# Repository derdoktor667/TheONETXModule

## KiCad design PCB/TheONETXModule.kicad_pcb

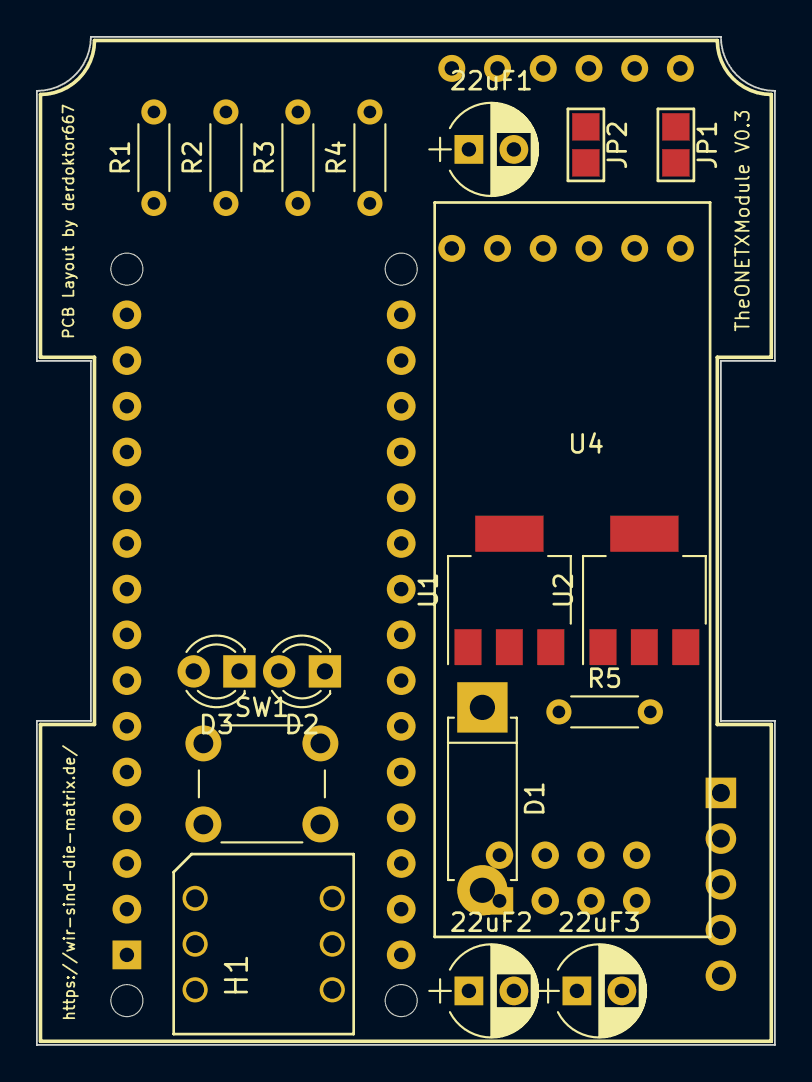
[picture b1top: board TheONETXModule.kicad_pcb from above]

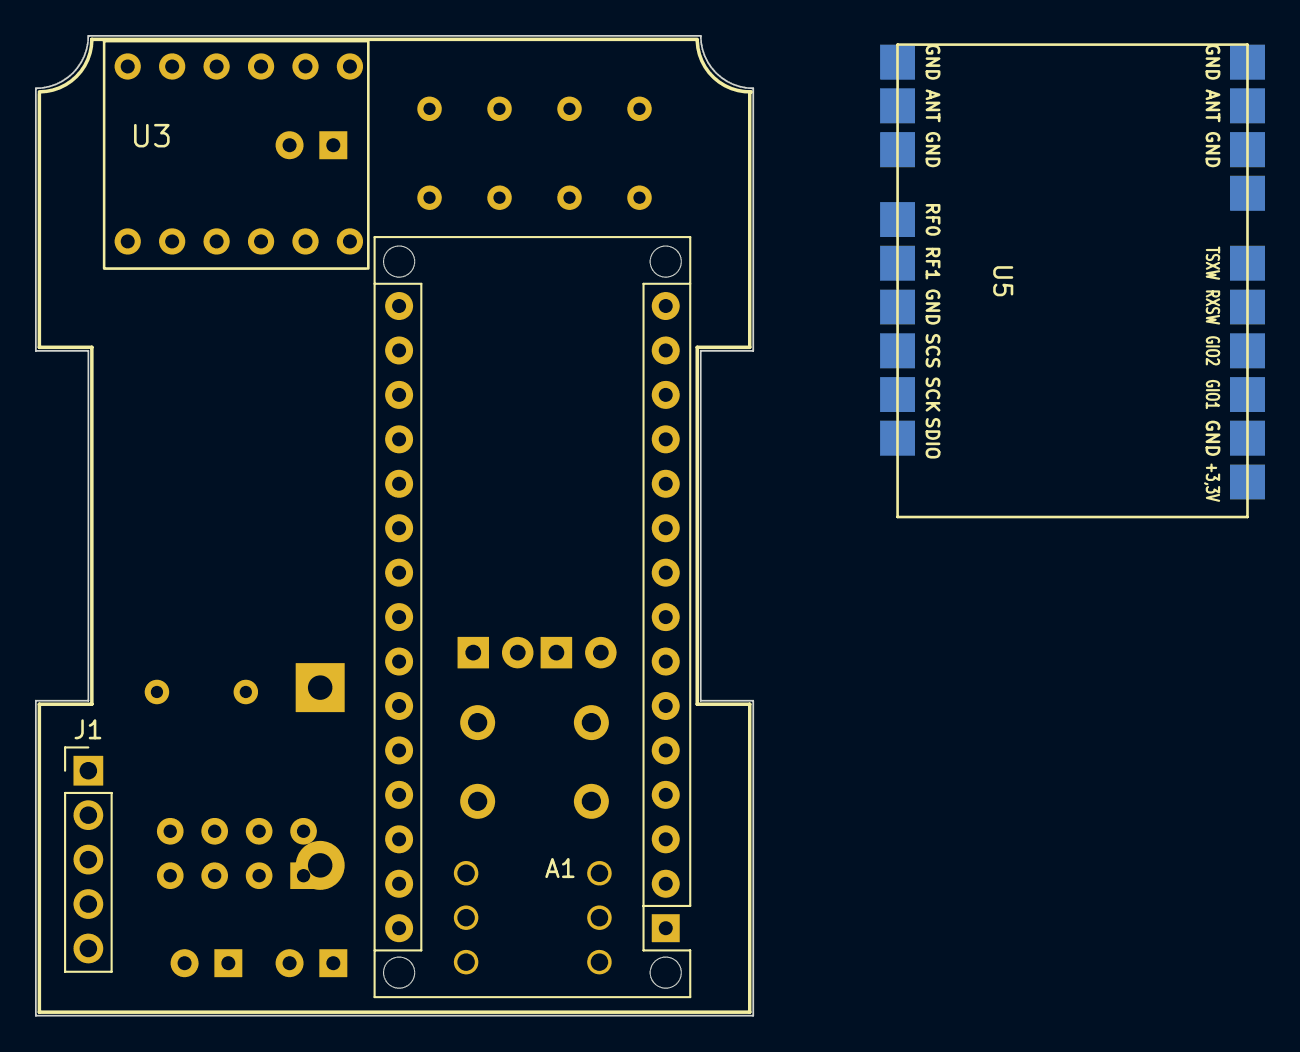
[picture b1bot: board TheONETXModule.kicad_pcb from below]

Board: 2 copper layers, 41.0 x 56.0 mm, 22 parts (4 on the bottom side), 28 nets, no tracks yet.

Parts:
22uF1, 22uF2, 22uF3: CP1; CP_Radial_D5.0mm_P2.50mm
A1: Arduino_Nano_v3.x; Arduino_Nano_WithMountingHoles
D1: D; D_5W_P10.16mm_Horizontal
D2, D3: LED; LED_D3.0mm
H1: HEX_CODER_16; HEX_ENCODER_16
J1: Conn_01x05_Female; Pin_Header_Straight_1x05_Pitch2.54mm
JP1: TEL_RX; Jumper_SMD
JP2: TEL_TX; Jumper_SMD
R1: 2.2K; R_Axial_DIN0204_L3.6mm_D1.6mm_P5.08mm_Horizontal
R2: 470; R_Axial_DIN0204_L3.6mm_D1.6mm_P5.08mm_Horizontal
R3, R4: 1K; R_Axial_DIN0204_L3.6mm_D1.6mm_P5.08mm_Horizontal
R5: 10K; R_Axial_DIN0204_L3.6mm_D1.6mm_P5.08mm_Horizontal
SW1: Bind Button; SW_PUSH_6mm
U1: L7805; SOT-223
U2: LD1117S33; SOT-223
U3: LogicShift; 4Ch-LogicShift
U4: NRF24L01; NRF24L01_PA
U5: A7105; A7106

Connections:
/3.3V: 22uF3.1, U2.2, U3.LV, U4.2, U4.3, U5.10
/5V: 22uF2.1, A1.30, R4.1, U1.3, U2.3, U3.HV
/5V_int: A1.27, R5.1
/A0: A1.19, H1.8
/A7105_CS: A1.5, U3.HV1
/A7105_CS_LV: U3.LV1, U5.17
/D10: A1.13, H1.1
/D11: A1.14, H1.2
/D12: A1.15, H1.4
/MISO: A1.9, U4.7
/MOSI: A1.8, U3.HV3, U4.6
/MOSI_LV: U3.LV3, U5.19
/NRF24_CS: A1.11, U4.4
/PB5: A1.16, R3.2, R5.2
/PPM: J1.1, R1.1
/PPM_IN: A1.6, JP1.1, R1.2
/RX_IN: A1.2, JP1.2
/SCK: A1.7, U3.HV2
/SCK_LV: U3.LV2, U4.5, U5.18
/TX_IN: A1.1, JP2.2
/VBAT+: 22uF1.1, D1.1, D1.2, J1.3, U1.1
GND: 22uF1.2, 22uF2.2, 22uF3.2, A1.4, A1.29, D2.1, D3.1, H1.C, J1.4, SW1.1, U1.2, U2.1, U3.GND, U4.1, U5.9
unnamed: D2.2, R4.2
unnamed: D3.2, R3.1, SW1.2
unnamed: J1.5, R2.1
unnamed: JP2.1, R2.2
unnamed: U5.5, U5.8
unnamed: U5.6, U5.7

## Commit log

2018-02-25 add some strucure
    ...structure
2018-02-25 Add a Website Container
    ---
2018-02-25 Set theme jekyll-theme-cayman
2018-04-10 PCB pushed to V 0.2
    ....created PCB for JR sized slot and already in beta testing ...PCB manufracted by AISLER
2018-07-09 ...bump
    ...bump
2019-01-30 Set theme jekyll-theme-slate
2019-05-21 KiCad Stuff
2022-11-10 ...update to new KiCAD 6.0
    ...custom layouts not loading!!!
